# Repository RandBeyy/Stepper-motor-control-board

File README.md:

# Respooler

A control board for an automatic filament respooler. Based on the **ATmega328P**, it drives two stepper motors, provides a simple user interface, and monitors filament feed from the donor spool.

## Photos

The assembled device in its enclosure.

The main board and display board as shown in KiCad.

## Features

- Two stepper motors: one rotates the receiving spool, while the other moves the filament guide to distribute filament evenly.
- Operation through a display and three buttons.
- Presets for different spool sizes and filament diameters.
- Estimates the wound filament length and weight based on the number of turns and configured parameters.
- An encoder monitors the donor spool. Winding stops if the spool stops turning, indicating that filament feed has ended.
- A buzzer signals when winding is complete.

The weight is an estimate calculated by the controller; it is not measured with a load cell.

## Hardware

This repository contains KiCad projects for the main controller board and a separate display board:

- `PCB/RespoolerPCB.kicad_pro` — main ATmega328P controller board.
- `PCB/DisplayPCB/DisplayShield/DisplayShield.kicad_pro` — display and button board.
- `PCB/Pictures/` — photos of the assembled device and board render.

The main board provides connections for two stepper drivers, an encoder, end stops, the display, buttons, a fan, and ISP programming. The display board is designed for an I²C SSD1306 OLED and has three control buttons.

## Project files

Open the relevant `.kicad_pro` file in KiCad to view the schematic and PCB layout. The local OLED footprint library is in `PCB/SSD1306.pretty/`.

> This repository currently contains the KiCad hardware design. Firmware and a separate assembly guide are not included.

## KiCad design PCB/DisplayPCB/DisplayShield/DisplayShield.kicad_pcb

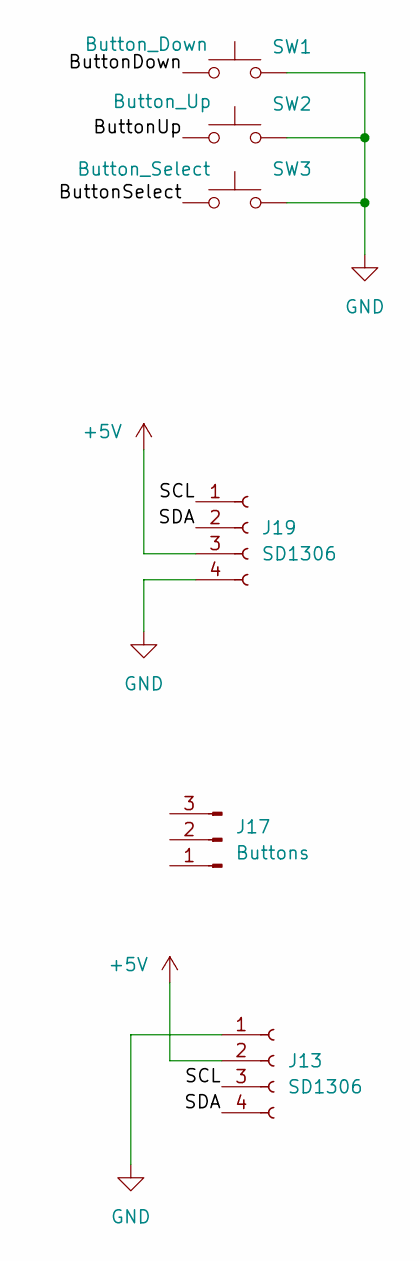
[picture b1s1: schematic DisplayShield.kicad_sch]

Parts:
J13: SD1306; 128x64OLED
J17: Buttons; PinHeader_1x03_P2.54mm_Vertical
J19: SD1306; PinSocket_1x04_P2.54mm_Vertical
SW1: Button_Down; SW_PUSH_6mm_H4.3mm
SW2: Button_Up; SW_PUSH_6mm_H4.3mm
SW3: Button_Select; SW_PUSH_6mm_H4.3mm

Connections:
+5V: J13.2, J19.3
/ButtonDown: J17.3, SW1.1
/ButtonSelect: J17.1, SW3.1
/ButtonUp: J17.2, SW2.1
/SCL: J13.3, J19.1
/SDA: J13.4, J19.2
GND: J13.1, J19.4, SW1.2, SW2.2, SW3.2

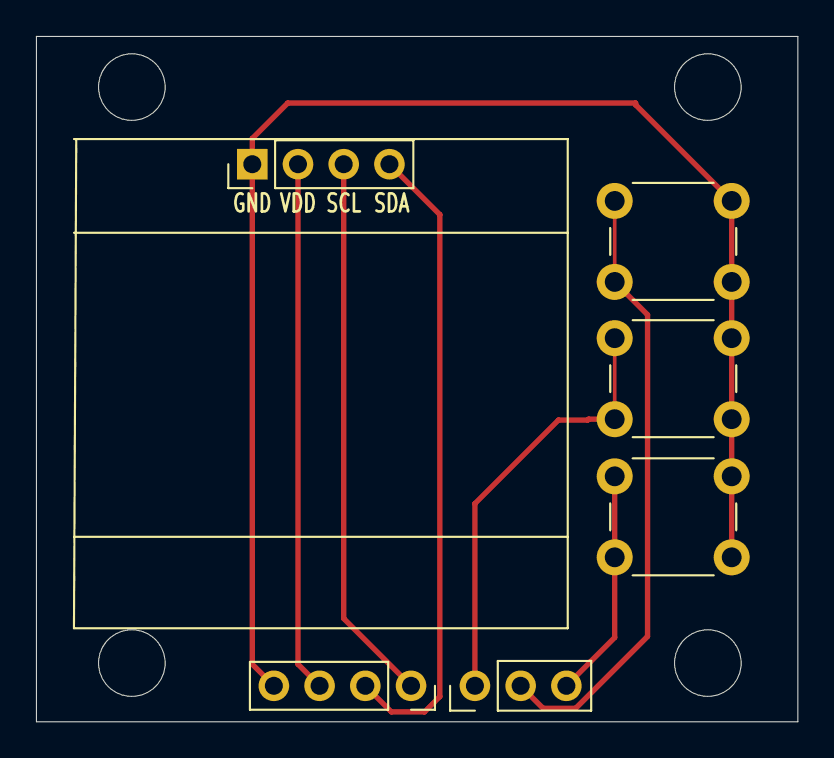
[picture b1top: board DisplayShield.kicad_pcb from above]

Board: 2 copper layers, 42.3 x 38.1 mm, 10 parts (0 on the bottom side), 7 nets.

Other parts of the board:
H5, H6, H7, H8: MountingHole; MountingHole_2.5mm

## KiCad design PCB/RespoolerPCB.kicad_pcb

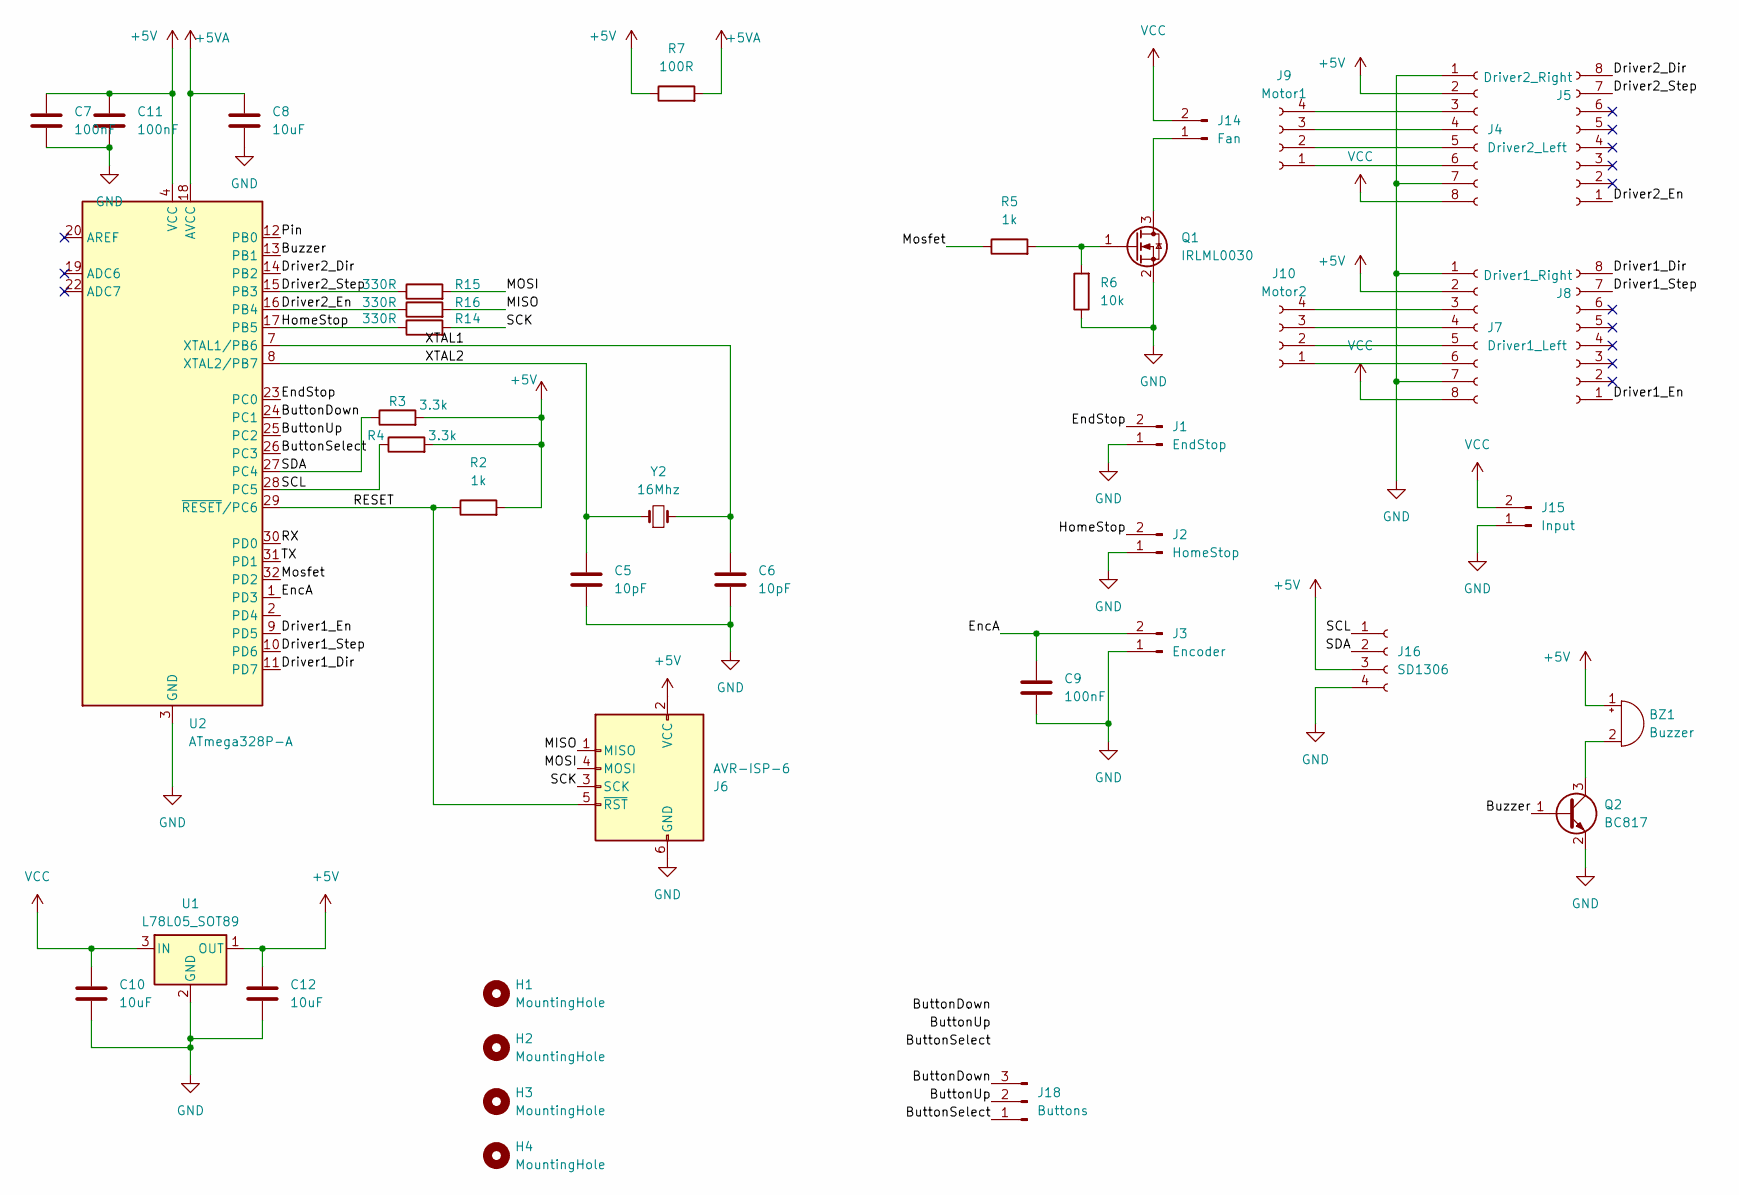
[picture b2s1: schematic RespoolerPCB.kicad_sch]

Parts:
BZ1: Buzzer; Buzzer_12x9.5RM7.6
C5, C6: 10pF; C_0603_1608Metric
C7, C9, C11: 100nF; C_0603_1608Metric
C8, C10, C12: 10uF; C_0603_1608Metric
H1, H2, H3, H4: MountingHole; MountingHole_3.2mm_M3
J1: EndStop; PinHeader_1x02_P2.54mm_Vertical
J2: HomeStop; PinHeader_1x02_P2.54mm_Vertical
J3: Encoder; PinHeader_1x02_P2.54mm_Vertical
J4: Driver2_Left; PinSocket_1x08_P2.54mm_Vertical
J5: Driver2_Right; PinSocket_1x08_P2.54mm_Vertical
J6: AVR-ISP-6; PinHeader_2x03_P2.54mm_Vertical
J7: Driver1_Left; PinSocket_1x08_P2.54mm_Vertical
J8: Driver1_Right; PinSocket_1x08_P2.54mm_Vertical
J9: Motor1; PinSocket_1x04_P2.54mm_Vertical
J10: Motor2; PinSocket_1x04_P2.54mm_Vertical
J14: Fan; PinHeader_1x02_P2.54mm_Vertical
J15: Input; PinHeader_1x02_P2.54mm_Vertical
J16: SD1306; PinSocket_1x04_P2.54mm_Vertical
J18: Buttons; PinHeader_1x03_P2.54mm_Vertical
Q1: IRLML0030; SOT-23
Q2: BC817; SOT-23
R2, R5: 1k; R_0603_1608Metric
R3, R4: 3.3k; R_0603_1608Metric
R6: 10k; R_0603_1608Metric
R7: 100R; R_0603_1608Metric
R14, R15, R16: 330R; R_0603_1608Metric
U1: L78L05_SOT89; SOT-89-3
U2: ATmega328P-A; TQFP-32_7x7mm_P0.8mm
Y2: 16Mhz; Crystal_SMD_5032-2Pin_5.0x3.2mm

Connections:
+5V: BZ1.1 (+), C7.1, C11.1, C12.1, J4.2, J6.2 (VCC), J7.2, J16.3, R2.2, R3.2, R4.2, R7.1, U1.1 (OUT), U2.4 (VCC), U2.6 (VCC)
+5VA: C8.1, R7.2, U2.18 (AVCC)
/ButtonDown: J18.3, U2.24 (PC1)
/ButtonSelect: J18.1, U2.26 (PC3)
/ButtonUp: J18.2, U2.25 (PC2)
/Buzzer: Q2.1 (B), U2.13 (PB1)
/Driver1_Dir: J8.8, U2.11 (PD7)
/Driver1_En: J8.1, U2.9 (PD5)
/Driver1_Step: J8.7, U2.10 (PD6)
/Driver2_Dir: J5.8, U2.14 (PB2)
/Driver2_En: J5.1, R16.1, U2.16 (PB4)
/Driver2_Step: J5.7, R15.1, U2.15 (PB3)
/EncA: C9.1, J3.2, U2.1 (PD3)
/EndStop: J1.2, U2.23 (PC0)
/HomeStop: J2.2, R14.1, U2.17 (PB5)
/MISO: J6.1 (MISO), R16.2
/MOSI: J6.4 (MOSI), R15.2
/Mosfet: R5.1, U2.32 (PD2)
/Pin: U2.12 (PB0)
/RESET: J6.5 (~RST), R2.1, U2.29 (~RESET/PC6)
/RX: U2.30 (PD0)
/SCK: J6.3 (SCK), R14.2
/SCL: J16.1, R4.1, U2.28 (PC5)
/SDA: J16.2, R3.1, U2.27 (PC4)
/TX: U2.31 (PD1)
/XTAL1: C6.1, U2.7 (XTAL1/PB6), Y2.2
/XTAL2: C5.1, U2.8 (XTAL2/PB7), Y2.1
GND: C5.2, C6.2, C7.2, C8.2, C9.2, C10.2, C11.2, C12.2, J1.1, J2.1, J3.1, J4.1, J4.7, J6.6 (GND), J7.1, J7.7, J15.1, J16.4, Q1.2 (S), Q2.2 (E), R6.1, U1.2 (GND), U2.3 (GND), U2.5 (GND), U2.21 (GND)
unnamed: BZ1.2 (-), Q2.3 (C)
unnamed: J4.3, J9.4
unnamed: J4.4, J9.3
unnamed: J4.5, J9.2
unnamed: J4.6, J9.1
unnamed: J7.6, J10.1
unnamed: J7.5, J10.2
unnamed: J7.4, J10.3
unnamed: J7.3, J10.4
unnamed: J14.1, Q1.3 (D)
unnamed: Q1.1 (G), R5.2, R6.2
VCC: C10.1, J4.8, J7.8, J14.2, J15.2, U1.3 (IN)

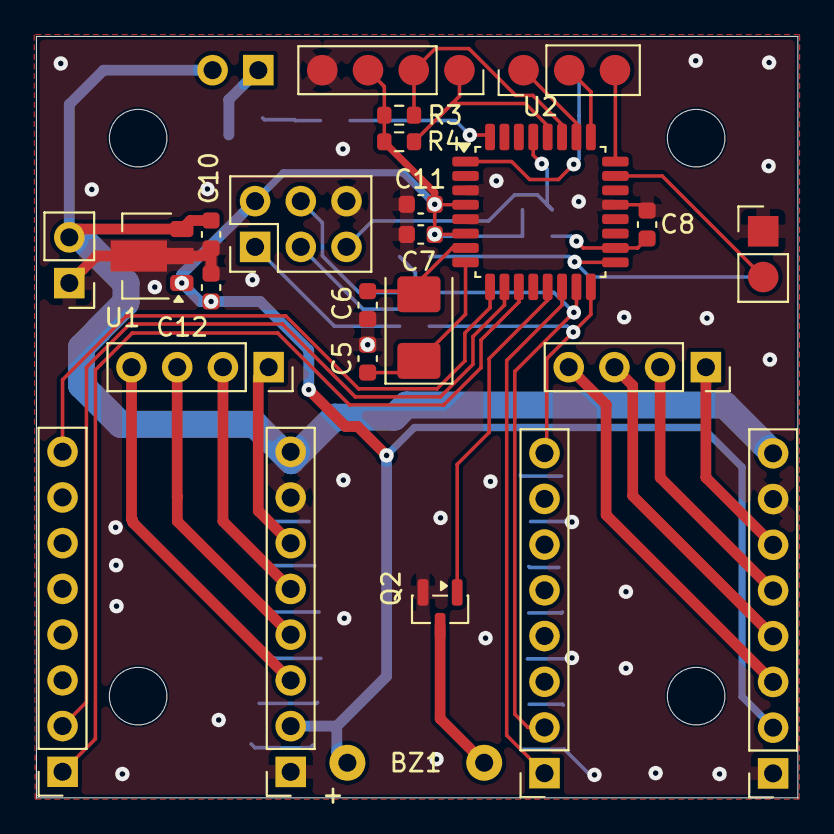
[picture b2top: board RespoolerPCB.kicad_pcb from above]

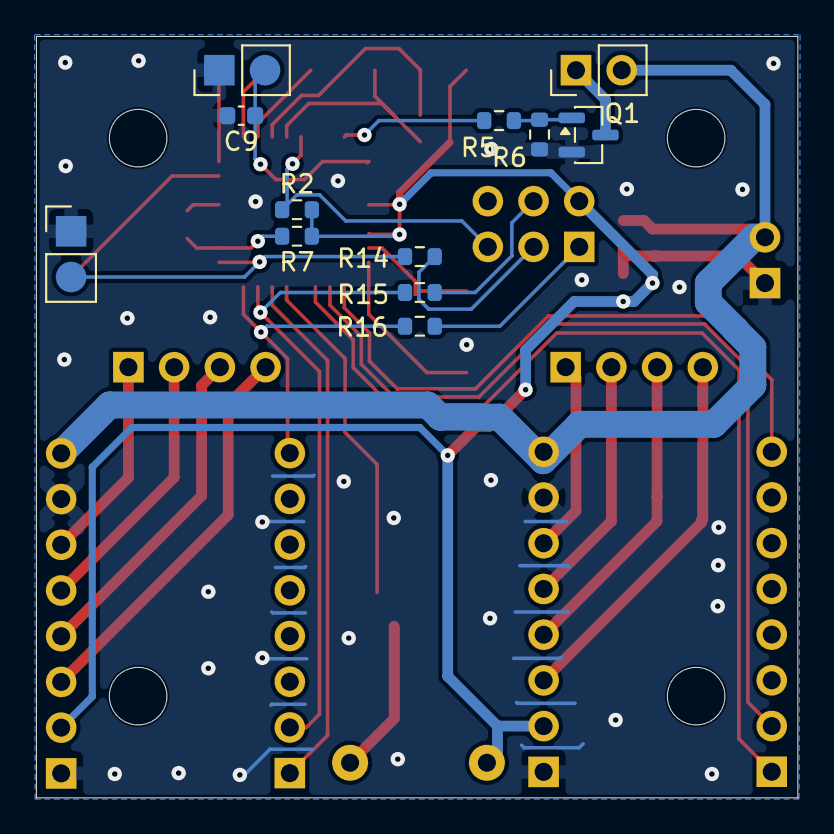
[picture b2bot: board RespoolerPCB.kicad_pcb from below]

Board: 2 copper layers, 42.3 x 42.3 mm, 41 parts (12 on the bottom side), 37 nets.
